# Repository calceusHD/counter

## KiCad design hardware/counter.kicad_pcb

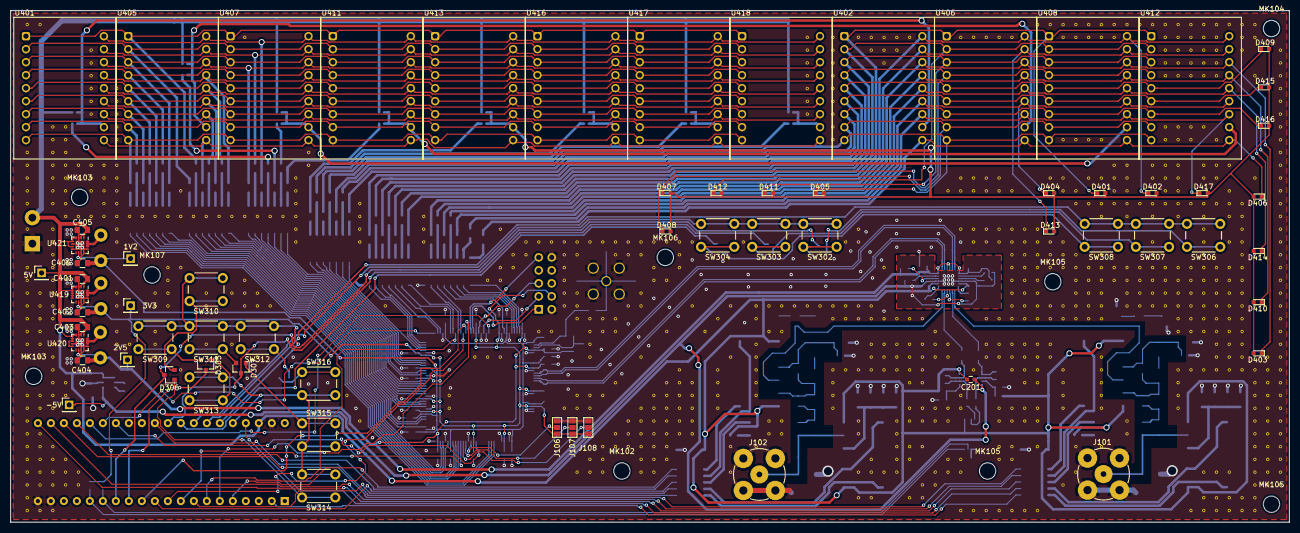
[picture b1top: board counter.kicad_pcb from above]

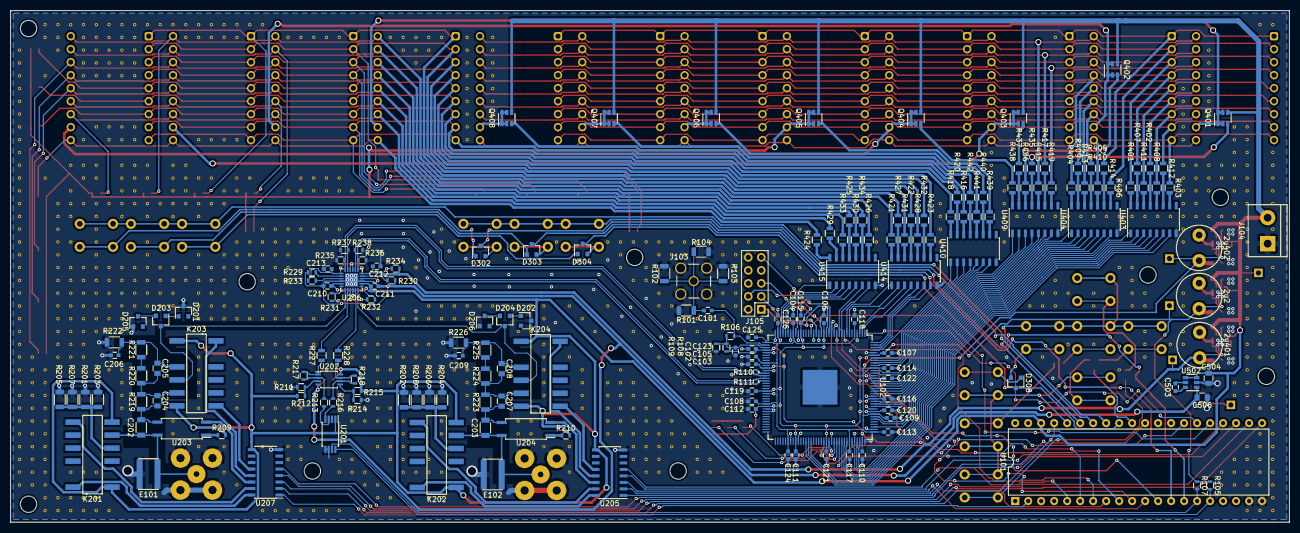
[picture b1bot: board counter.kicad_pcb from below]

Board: 2 copper layers, 250.0 x 100.0 mm, 1050 parts (178 on the bottom side), 249 nets.

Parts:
1V2, 2V5, 3V3, 5V: Test_Point; Pin_Header_Straight_1x01_Pitch2.54mm
2u2, 2u401, 2u402: L_Core_Ferrite; L_Radial_D8.7mm_P5.00mm_Fastron_07HCP
-5V: Test_Point; Pin_Header_Straight_1x01_Pitch2.54mm
C101, C102, C103, C104, C105, C106, C107, C108, C109, C110, C111, C112, C113, C114, C115, C116, C117, C118, C119, C120, C121, C122, C123, C124, C125, C126, C201, C210, C211, C212, C213: 100n; C_0603
C202, C203: 47n 350V; C_1206
C204, C205, C207, C208: 22p; C_0805
C206, C209: 220p; C_0603
C401, C402, C403, C404, C405, C406, C504, C506: 10u 6.3V; C_0805
C503: 1u; C_0603
D201, D202, D205, D206: BZX84C3V6LT1G; D_SOT-23_ANK
D203, D204: BAR64-04; SOT-23
D302, D303, D304, D305, D306, D307, D308: D_x2_ACom_KKA; SOT-23
D401, D402, D403, D404, D405, D406, D407, D408, D409, D410, D411, D412, D413, D414, D415, D416, D417: SML-D12Y1WT86; LED_0603
E101, E102: SPARK_GAP; B88069X4911T902
J101, J102: Conn_Coaxial; BNC-5-1634503-1
J103: Conn_Coaxial; SMA_THT_Jack_Straight
J104: Screw_Terminal_01x02; TerminalBlock_bornier-2_P5.08mm
J105: Conn_02x05_Odd_Even; Pin_Header_Straight_2x05_Pitch2.54mm
J106, J107, J108: GS3
K201, K202, K203, K204: EE2-*TNU; Relay_DPDT_DCLT
MK102, MK103, MK103#2, MK104, MK105, MK105#2, MK105#3, MK106, MK107: Mounting_Hole; MountingHole_3.2mm_M3_ISO7380
Q401, Q402, Q403, Q404, Q405, Q406, Q407, Q408: ZXTP2006E6; SOT-23-6
R101, R102, R103, R104, R201, R202, R203, R204, R205, R206, R207, R208: 200; R_1206
R105, R107, R108, R109: 1k; R_0603
R106: 5k; R_0603
R110, R111: 100; R_0402
R209, R210: 680; R_0603
R211, R214, R217, R218: 20k; R_0603
R212, R213, R215, R216, R229, R230, R233, R234: 10k; R_0603
R219, R223: 510k; R_1206
R220, R224: 390k; R_1206
R221, R222, R225, R226: 50k; R_1206
R227, R228, R435, R436, R437, R438, R439, R440, R441, R442: 150; R_0805
R231, R232: 22k; R_0603
R235, R236, R237, R238: 82; R_0603
R401, R402, R403, R404, R405, R406, R407, R408, R409, R410, R411, R412, R413, R414, R415, R416, R417, R418, R419, R420, R421, R422, R423, R424, R425, R426, R427, R428, R429, R430, R431, R432, R433, R434: 18; R_0805
SW302, SW303, SW304, SW306, SW307, SW308, SW309, SW310, SW311, SW312, SW313, SW314, SW315, SW316: SW_Push; SW_PUSH_6mm
U101: STM32_BLUEPILL; DIP-40_W15.24mm
U102: 10CL006ZE144I8G; EQFP-144_20x20mm_Pitch0.5mm
U201: MCP47FEB02; TSSOP-8_4.4x3mm_Pitch0.65mm
U202: TL972; TSSOP-8_3x3mm_Pitch0.65mm
U203, U204: LH1546; SO-4_7.6x3.6mm_Pitch2.54mm
U205, U207, U403, U404, U409, U410, U414, U415: MC1413; SOIC-16_3.9x9.9mm_Pitch1.27mm
U206: LMH7322; QFN-24-1EP_4x4mm_Pitch0.5mm
U401, U402, U405, U406, U407, U408, U411, U412, U413, U416, U417, U418: 16Segment
U419, U420, U421: SC183C; QFN-16-1EP_3x3mm_Pitch0.5mm
U502: LM2776; SOT-23-6
V2_2, V2_12, V2_13, V2_14, V2_15, V2_16, V2_18, V2_21, V2_22, V2_23, V2_24, V2_25, V2_26, V2_27, V2_28, V2_31, V2_32, V2_33, V2_34, V2_35, V2_36, V2_37, V2_38, V2_39, V2_40, V3_2, V3_23, V3_24, V3_25, V3_26, V3_27, V3_28, V3_31, V3_32, V3_34, V3_35, V3_36, V3_37, V3_38, V3_40, V4_10, V4_11, V4_12, V4_13, V4_14, V4_15, V4_16, V4_18, V4_19, V4_20, V4_21, V4_22, V4_23, V4_24, V4_25, V4_27, V4_28, V4_29, V4_30, V4_31, V4_32, V4_35, V4_36, V4_37, V4_38, V4_40, V5_10, V5_11, V5_12, V5_13, V5_14, V5_15, V5_16, V5_17, V5_30, V5_31, V5_36, V5_37, V5_38, V6_13, V6_14, V6_17, V6_37, V6_38, V7_4, V7_5, V7_6, V7_7, V7_8, V7_9, V7_13, V7_14, V7_15, V7_17, V8_13, V8_14, V8_15, V8_16, V8_17, V9_7, V9_8, V9_9, V9_10, V9_11, V9_13, V9_14, V9_15, V9_16, V9_17, V9_18, V9_19, V9_23, V9_24, V9_26, V9_27, V10_17, V10_27, V11_17, V12_17, V12_23, V12_24, V12_26, V12_27, V12_28, V13_17, V13_21, V13_22, V13_23, V13_24, V14_15, V14_17, V14_21, V14_29, V15_17, V16_17, V16_23, V16_24, V16_27, V17_17, V18_17, V18_23, V18_27, V19_3, V19_17, V19_22, V19_23, V19_24, V20_17, V20_23, V20_24, V20_28, V21_17, V21_24, V22_17, V23_14, V23_15, V23_16, V23_17, V23_18, V23_19, V24_12, V24_13, V27_31, V28_16, V28_17, V28_18, V28_19, V28_33, V30_24, V33_17, V33_18, V33_19, V35_31, V35_32, V37_28, V38_22, V38_28, V39_18, V39_21, V39_22, V39_28, V40_20, V40_21, V41_19, V41_20, V42_19, V42_26, V43_19, V43_26, V44_19, V44_20, V44_21, V44_22, V44_23, V44_24, V44_32, V45_19, V45_20, V45_23, V45_24, V45_25, V45_31, V45_32, V45_37, V46_19, V46_25, V46_26, V46_27, V46_28, V46_31, V46_32, V46_36, V46_37, V47_19, V47_25, V47_26, V47_31, V47_35, V47_36, V47_37, V48_19, V48_20, V48_25, V48_26, V48_30, V48_34, V48_35, V49_19, V49_20, V49_24, V49_33, V49_34, V49_35, V50_19, V50_20, V50_23, V50_24, V50_28, V50_32, V50_33, V50_34, V50_35, V50_36, V50_37, V51_19, V51_21, V51_22, V51_31, V51_32, V51_33, V51_34, V51_35, V51_36, V51_37, V52_19, V52_22, V52_26, V52_30, V52_31, V52_32, V52_33, V52_34, V52_35, V52_36, V53_19, V53_20, V53_21, V53_29, V53_30, V53_31, V53_32, V53_33, V53_34, V54_19, V54_24, V54_30, V54_31, V54_32, V54_33, V54_34, V55_26, V56_25, V56_29, V56_30, V56_31, V56_32, V57_24, V57_28, V57_35, V57_37, V58_19, V59_24, V59_25, V59_27, V59_28, V59_29, V59_30, V59_31, V59_35, V60_24, V60_26, V60_33, V60_34, V61_24, V61_26, V61_33, V61_34, V62_24, V63_3, V63_4, V63_5, V63_6, V63_7, V63_8, V63_9, V63_24, V64_24, V65_3, V65_4, V65_5, V65_6, V65_7, V65_8, V65_9, V65_10, V65_11, V65_24, V65_25, V65_29, V65_30, V65_31, V65_32, V66_19, V66_24, V66_25, V66_29, V67_3, V67_18, V67_19, V67_24, V67_25, V67_29, V67_33, V67_34, V67_37, V67_39, V68_3, V68_4, V68_24, V68_25, V68_27, V68_28, V68_29, V68_36, V68_37, V68_39, V69_3, V69_4, V69_5, V69_21, V69_25, V69_27, V69_28, V69_29, V69_37, V70_3, V70_4, V70_25, V70_27, V70_28, V70_29, V70_33, V70_34, V70_35, V70_36, V70_37, V71_3, V71_25, V71_27, V71_28, V71_29, V71_30, V71_32, V71_33, V71_35, V71_36, V71_39, V72_25, V72_27, V72_28, V72_29, V72_30, V72_32, V72_33, V72_35, V72_38, V72_39, V73_26, V73_27, V73_28, V73_32, V73_33, V73_37, V73_38, V74_15, V74_27, V74_28, V74_32, V74_33, V74_36, V74_37, V74_37#2, V75_3, V75_14, V75_15, V75_18, V75_31, V75_32, V75_36, V75_40, V76_3, V76_14, V76_15, V76_18, V76_19, V76_29, V76_40, V77_3, V77_14, V77_15, V77_18, V77_19, V77_25, V77_27, V77_28, V77_40, V78_3, V78_14, V78_15, V78_18, V78_19, V78_25, V78_27, V78_28, V78_32, V78_33, V78_35, V78_36, V78_40, V79_3, V79_15, V79_18, V79_19, V79_20, V79_21, V79_22, V79_23, V79_24, V79_25, V79_27, V79_28, V79_29, V79_32, V79_33, V79_35, V79_36, V79_40, V80_18, V80_19, V80_20, V80_21, V80_22, V80_23, V80_24, V80_25, V80_27, V80_28, V80_29, V80_30, V80_32, V80_33, V80_40, V81_2, V81_18, V81_19, V81_20, V81_21, V81_22, V81_23, V81_24, V81_25, V81_27, V81_28, V81_29, V81_30, V81_32, V81_33, V81_35, V81_40, V82_2, V82_14, V82_19, V82_20, V82_21, V82_24, V82_25, V82_27, V82_28, V83_2, V83_3, V83_11, V83_14, V83_15, V83_19, V83_20, V83_21, V83_24, V83_25, V83_29, V83_30, V83_31, V83_32, V83_38, V84_2, V84_3, V84_11, V84_15, V84_16, V84_20, V84_21, V84_22, V84_23, V84_24, V84_25, V84_35, V84_37, V85_2, V85_3, V85_11, V85_14, V85_16, V85_21, V85_22, V85_23, V85_24, V85_25, V86_2, V86_3, V86_11, V86_14, V86_16, V86_17, V86_20, V86_21, V86_22, V86_23, V86_24, V86_25, V86_28, V86_29, V86_30, V86_31, V86_32, V86_35, V87_2, V87_3, V87_13, V87_14, V87_15, V87_16, V87_21, V87_22, V88_2, V88_13, V88_14, V88_15, V88_16, V88_17, V88_21, V88_22, V88_23, V88_24, V88_33, V88_34, V89_2, V89_16, V89_21, V89_22, V89_23, V89_24, V90_2, V90_13, V90_14, V90_16, V90_17, V90_19, V90_20, V90_21, V90_22, V90_23, V90_24, V91_2, V91_3, V91_4, V91_5, V91_6, V91_10, V91_11, V91_13, V91_14, V91_15, V91_16, V91_21, V91_22, V91_23, V91_24, V92_2, V92_3, V92_4, V92_5, V92_6, V92_10, V92_11, V92_13, V92_14, V92_15, V92_16, V92_17, V92_21, V92_22, V92_23, V92_24, V92_25, V92_26, V92_29, V92_30, V92_31, V92_32, V93_2, V93_3, V93_4, V93_5, V93_6, V93_10, V93_11, V93_16, V93_21, V93_22, V93_23, V93_24, V93_25, V93_26, V93_29, V93_40, V94_2, V94_3, V94_4, V94_5, V94_6, V94_10, V94_13, V94_14, V94_16, V94_17, V94_18, V94_19, V94_20, V94_21, V94_22, V94_23, V94_24, V94_25, V94_26, V94_29, V94_37, V94_39, V94_40, V95_2, V95_3, V95_4, V95_5, V95_6, V95_11, V95_13, V95_14, V95_16, V95_21, V95_22, V95_23, V95_24, V95_25, V95_26, V95_27, V95_28, V95_29, V95_37, V95_39, V95_40, V96_2, V96_13, V96_15, V96_16, V96_17, V96_19, V96_21, V96_22, V96_23, V96_24, V96_25, V96_26, V96_27, V96_28, V96_29, V96_37, V96_39, V96_40, V97_2, V97_3, V97_4, V97_16, V97_17, V97_18, V97_19, V97_20, V97_21, V97_22, V97_23, V97_24, V97_25, V97_26, V97_27, V97_28, V97_29, V97_39, V97_40, V98_2, V98_3, V98_6, V98_14, V98_29, V98_30, V98_31, V98_32, V98_33, V98_34, V98_35, V98_36, V98_37, V98_38, V98_39, V98_40, V99_28, V99_29, V99_30, V99_31, V99_32, V99_33, V99_34, V99_35, V99_36, V99_37, V99_38, V100_4, V100_5, V100_6, V100_7, V100_8, V100_9, V100_10, V100_11, V100_12, V100_13, V100_14, V100_15, V100_16, V100_17, V100_18, V100_19, V100_20, V100_21, V100_22, V100_23, V100_24, V100_25, V100_26, V100_27, V100_28, V100_29, V100_30, V100_31, V100_32, V100_33, V100_34, V100_35, V100_36, V100_37, V100_38: AUTO_VIA; VIA_MATRIX

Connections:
+1V2: 1V2.1, 2u402.2, C103.1, C104.2, C108.1, C109.2, C113.1, C114.2, C117.1, C118.2, C124.2, C125.2, C406.2, U102.5, U102.29, U102.37, U102.45, U102.61, U102.78, U102.102, U102.109, U102.116, U102.134, U421.10
+2V5: 2V5.1, 2u401.2, C105.2, C110.2, C123.2, C126.2, C212.2, C213.2, C404.2, R108.1, R233.2, R234.2, U102.35, U102.40, U102.47, U102.107, U206.1, U206.18, U206.21, U206.22, U420.10
+3V3: 2u2.2, 3V3.1, C106.2, C107.2, C111.2, C112.2, C115.2, C116.2, C119.2, C120.2, C121.2, C122.2, C402.2, J105.4, J106.3, J107.3, J108.3, R105.1, R107.1, U102.17, U102.26, U102.56, U102.62, U102.81, U102.93, U102.117, U102.122, U102.130, U102.139, U419.10
+5V: 5V.1, C201.2, C210.1, C211.1, C401.2, C403.2, C405.2, C504.1, J104.2, K201.1, K201.6, K202.1, K202.6, K203.1, K203.6, K204.1, K204.6, Q401.4, Q402.4, Q403.4, Q404.4, Q405.4, Q406.4, Q407.4, Q408.4, R209.2, R210.2, R212.2, R215.2, U101.38, U201.1, U202.8, U205.9, U206.5, U206.14, U207.9, U419.1, U419.2, U419.4, U419.5, U419.6, U419.7, U419.8, U420.1, U420.2, U420.4, U420.5, U420.6, U420.8, U421.1, U421.2, U421.4, U421.5, U421.7, U502.3, U502.4
-5V: -5V.1, C201.1, C210.2, C211.2, C506.2, R229.2, R230.2, U202.4, U206.4, U206.15, U206.25, U502.1
/50Ohm_OFF_1: U101.37, U207.2
/50Ohm_OFF_2: U101.8, U205.2
/50Ohm_ON_1: U101.2, U207.1
/50Ohm_ON_2: U101.30, U205.1
/A0: U102.126, U409.4
/A1: U102.127, U409.3
/A2: U102.128, U409.2
/A3: U102.129, U409.1
/A4: U102.132, U410.7
/A5: U102.133, U410.6
/A6: U102.135, U410.5
/A7: U102.136, U410.4
/AC_1: U101.21, U207.3
/AC_2: U101.11, U205.3
/AFE/50Ohm_OFF_1_int: K201.7, U207.15
/AFE/50Ohm_OFF_2_int: K202.7, U205.15
/AFE/50Ohm_ON_1_int: K201.12, U207.16
/AFE/50Ohm_ON_2_int: K202.12, U205.16
/AFE/AC_1_int: U203.2, U207.14
/AFE/AC_2_int: U204.2, U205.14
/AFE/CH1_IN: C202.2, E101.1, J101.1, K201.5, U203.4
/AFE/CH2_IN: C203.2, E102.1, J102.1, K202.5, U204.4
/AFE/DIV10_OFF_1_int: K203.7, U207.12
/AFE/DIV10_OFF_2_int: K204.7, U205.12
/AFE/DIV10_ON_1_int: K203.12, U207.13
/AFE/DIV10_ON_2_int: K204.12, U205.13
/AFE/VOFF2: R228.1, U206.11
/AFE/VOFF_1: R227.1, U206.8
/C0: SW302.2, SW303.2, SW304.2, U101.33
/C0_1: U102.106, U404.6
/C0_2: U102.7, U414.2
/C1: SW306.2, SW307.2, SW308.2, U101.34
/C1_1: U102.125, U409.5
/C1_2: U102.8, U414.1
/C2: SW309.2, SW310.2, SW311.2, SW312.2, U101.35
/C2_1: U102.121, U409.7
/C2_2: U102.11, U415.6
/C3: SW313.2, SW314.2, SW315.2, SW316.2, U101.36
/C3_1: U102.115, U404.3
/C3_2: U102.32, U415.3
/C4_1: U102.85, U403.7
/C4_2: U102.137, U410.3
/C5_1: U102.111, U404.5
/C5_2: U102.34, U415.1
/C6_1: U102.86, U403.6
/C6_2: U102.138, U410.2
/C7_1: U102.101, U403.2
/C7_2: U102.144, U414.5
/C8_1: U102.100, U403.3
/C8_2: U102.143, U414.6
/C9_1: U102.120, U404.1
/C9_2: U102.28, U415.5
/C10_1: U102.103, U403.1
/C10_2: U102.2, U414.4
/C11_1: U102.105, U404.7
/C11_2: U102.3, U414.3
/C12_1: U102.124, U409.6
/C12_2: U102.10, U415.7
/C13_1: U102.119, U404.2
/C13_2: U102.31, U415.4
/C14_1: U102.99, U403.4
/C14_2: U102.142, U414.7
/C15_1: U102.87, U403.5
/C15_2: U102.141, U410.1
/C16_1: U102.114, U404.4
/C16_2: U102.33, U415.2
/CH1+: R110.2, R237.2, U102.50, U206.23
/CH1-: R110.1, R235.2, U102.49, U206.24
/CH2+: R111.2, R238.2, U102.51, U206.20
/CH2-: R111.1, R236.2, U102.52, U206.19
/CLKIN_n: C102.2, R106.2, R108.2, R109.1, U102.39
/CLKIN_p: C101.1, R106.1, U102.38
/CONF_DONE: U101.27, U102.92
/DATA0: U101.12, U102.13
/DCLK: U101.10, U102.12
/DIV10_OFF_1: U101.23, U207.5
/DIV10_OFF_2: U101.5, U205.5
/DIV10_ON_1: U101.22, U207.4
/DIV10_ON_2: U101.24, U205.4
/INIT_DONE: U101.9, U102.98
/INTCLK: U101.25, U102.22
/LED_array/A0: Q401.1, Q401.2, Q401.5, Q401.6, U401.11, U402.11
/LED_array/A1: Q402.1, Q402.2, Q402.5, Q402.6, U405.11, U406.11
/LED_array/A1_1: R414.1, U401.1, U405.1, U407.1, U411.1, U413.1, U416.1, U417.1, U418.1
/LED_array/A1_2: D401.1, R427.1, U402.1, U406.1, U408.1, U412.1
/LED_array/A2: Q403.1, Q403.2, Q403.5, Q403.6, U407.11, U408.11
/LED_array/A2_1: R415.1, U401.18, U405.18, U407.18, U411.18, U413.18, U416.18, U417.18, U418.18
/LED_array/A2_2: D402.1, R421.1, U402.18, U406.18, U408.18, U412.18
/LED_array/A3: Q404.1, Q404.2, Q404.5, Q404.6, U411.11, U412.11
/LED_array/A4: D401.2, D402.2, D403.2, D404.2, D405.2, D406.2, D407.2, D408.2, D409.2, D410.2, D411.2, D412.2, D413.2, D414.2, D415.2, D416.2, D417.2, Q405.1, Q405.2, Q405.5, Q405.6, U413.11
/LED_array/A5: Q406.1, Q406.2, Q406.5, Q406.6, U416.11
/LED_array/A6: Q407.1, Q407.2, Q407.5, Q407.6, U417.11
/LED_array/A7: Q408.1, Q408.2, Q408.5, Q408.6, U418.11
/LED_array/B_1: R419.1, U401.16, U405.16, U407.16, U411.16, U413.16, U416.16, U417.16, U418.16
/LED_array/B_2: D403.1, R434.1, U402.16, U406.16, U408.16, U412.16
/LED_array/C_1: R413.1, U401.13, U405.13, U407.13, U411.13, U413.13, U416.13, U417.13, U418.13
/LED_array/C_2: D404.1, R433.1, U402.13, U406.13, U408.13, U412.13
/LED_array/D1_1: R403.1, U401.9, U405.9, U407.9, U411.9, U413.9, U416.9, U417.9, U418.9
/LED_array/D1_2: D405.1, R416.1, U402.9, U406.9, U408.9, U412.9
/LED_array/D2_1: R410.1, U401.10, U405.10, U407.10, U411.10, U413.10, U416.10, U417.10, U418.10
/LED_array/D2_2: D406.1, R424.1, U402.10, U406.10, U408.10, U412.10
/LED_array/DP_1: R405.1, U401.12, U405.12, U407.12, U411.12, U413.12, U416.12, U417.12, U418.12
/LED_array/DP_2: D417.1, R429.1, U402.12, U406.12, U408.12, U412.12
/LED_array/DR0: R435.2, U409.13
/LED_array/DR1: R436.2, U409.14
/LED_array/DR2: R437.2, U409.15
/LED_array/DR3: R438.2, U409.16
/LED_array/DR4: R439.2, U410.10
/LED_array/DR5: R440.2, U410.11
/LED_array/DR6: R441.2, U410.12
/LED_array/DR7: R442.2, U410.13
/LED_array/E_1: R412.1, U401.8, U405.8, U407.8, U411.8, U413.8, U416.8, U417.8, U418.8
/LED_array/E_2: D407.1, R420.1, U402.8, U406.8, U408.8, U412.8
/LED_array/F_1: R407.1, U401.4, U405.4, U407.4, U411.4, U413.4, U416.4, U417.4, U418.4
/LED_array/F_2: D408.1, R428.1, U402.4, U406.4, U408.4, U412.4
/LED_array/G1_1: R411.1, U401.5, U405.5, U407.5, U411.5, U413.5, U416.5, U417.5, U418.5
/LED_array/G1_2: D409.1, R432.1, U402.5, U406.5, U408.5, U412.5
/LED_array/G2_1: R404.1, U401.15, U405.15, U407.15, U411.15, U413.15, U416.15, U417.15, U418.15
/LED_array/G2_2: D410.1, R430.1, U402.15, U406.15, U408.15, U412.15
/LED_array/H_1: R401.1, U401.3, U405.3, U407.3, U411.3, U413.3, U416.3, U417.3, U418.3
/LED_array/H_2: D411.1, R422.1, U402.3, U406.3, U408.3, U412.3
/LED_array/J_1: R406.1, U401.2, U405.2, U407.2, U411.2, U413.2, U416.2, U417.2, U418.2
/LED_array/J_2: D412.1, R431.1, U402.2, U406.2, U408.2, U412.2
/LED_array/K_1: R417.1, U401.17, U405.17, U407.17, U411.17, U413.17, U416.17, U417.17, U418.17
/LED_array/K_2: D413.1, R426.1, U402.17, U406.17, U408.17, U412.17
/LED_array/L_1: R409.1, U401.14, U405.14, U407.14, U411.14, U413.14, U416.14, U417.14, U418.14
/LED_array/L_2: D414.1, R425.1, U402.14, U406.14, U408.14, U412.14
/LED_array/M_1: R402.1, U401.6, U405.6, U407.6, U411.6, U413.6, U416.6, U417.6, U418.6
/LED_array/M_2: D415.1, R423.1, U402.6, U406.6, U408.6, U412.6
/LED_array/N_1: R408.1, U401.7, U405.7, U407.7, U411.7, U413.7, U416.7, U417.7, U418.7
/LED_array/N_2: D416.1, R418.1, U402.7, U406.7, U408.7, U412.7
/MSEL0: J106.2, U102.94
/MSEL1: J107.2, U102.96
/MSEL2: J108.2, U102.97
/R0: D305.3, U101.13
/R1: D302.3, D306.3, U101.14
/R2: D303.3, D307.3, U101.31
/R3: D304.3, D308.3, U101.32
/SCL: R107.2, U101.15, U201.7
/SDA: R105.2, U101.16, U201.8
/TCK: J105.1, U102.16
/TDI: J105.9, U102.15
/TDO: J105.3, U102.20
/TMS: J105.5, U102.18
/TXD: U101.26, U102.1
/~CONFIG: U101.6, U102.14
/~STATUS: U101.7, U102.9
GND: C102.1, C103.2, C104.1, C105.1, C106.1, C107.1, C108.2, C109.1, C110.1, C111.1, C112.1, C113.2, C114.1, C115.1, C116.1, C117.2, C118.1, C119.1, C120.1, C121.1, C122.1, C123.1, C124.1, C125.1, C126.1, C206.1, C209.1, C212.1, C213.1, C401.1, C402.1, C403.1, C404.1, C405.1, C406.1, C504.2, C506.1, D201.1, D202.1, D205.2, D206.2, E101.2, E102.2, J101.2, J102.2, J103.2, J104.1, J105.2, J105.10, J106.1, J107.1, J108.1, R101.2, R102.2, R103.2, R104.2, R109.2, R201.2, R202.2, R203.2, R204.2, R205.2, R206.2, R207.2, R208.2, R211.2, R214.2, R222.2, R226.2, R235.1, R236.1, R237.1, R238.1, U101.19, U101.20, U101.39, U102.4, U102.19, U102.21, U102.27, U102.30, U102.36, U102.41, U102.48, U102.57, U102.63, U102.64, U102.79, U102.82, U102.95, U102.104, U102.108, U102.110, U102.118, U102.123, U102.131, U102.140, U102.145, U201.5, U201.6, U205.8, U207.8, U403.8, U404.8, U409.8, U410.8, U414.8, U415.8, U419.3, U419.11, U419.12, U419.13, U419.17, U420.3, U420.7, U420.11, U420.12, U420.13, U420.17, U421.3, U421.6, U421.8, U421.11, U421.12, U421.13, U421.17, U502.2, V2_2.1, V2_12.1, V2_13.1, V2_14.1, V2_15.1, V2_16.1, V2_18.1, V2_21.1, V2_22.1, V2_23.1, V2_24.1, V2_25.1, V2_26.1, V2_27.1, V2_28.1, V2_31.1, V2_32.1, V2_33.1, V2_34.1, V2_35.1, V2_36.1, V2_37.1, V2_38.1, V2_39.1, V2_40.1, V3_2.1, V3_23.1, V3_24.1, V3_25.1, V3_26.1, V3_27.1, V3_28.1, V3_31.1, V3_32.1, V3_34.1, V3_35.1, V3_36.1, V3_37.1, V3_38.1, V3_40.1, V4_10.1, V4_11.1, V4_12.1, V4_13.1, V4_14.1, V4_15.1, V4_16.1, V4_18.1, V4_19.1, V4_20.1, V4_21.1, V4_22.1, V4_23.1, V4_24.1, V4_25.1, V4_27.1, V4_28.1, V4_29.1, V4_30.1, V4_31.1, V4_32.1, V4_35.1, V4_36.1, V4_37.1, V4_38.1, V4_40.1, V5_10.1, V5_11.1, V5_12.1, V5_13.1, V5_14.1, V5_15.1, V5_16.1, V5_17.1, V5_30.1, V5_31.1, V5_36.1, V5_37.1, V5_38.1, V6_13.1, V6_14.1, V6_17.1, V6_37.1, V6_38.1, V7_4.1, V7_5.1, V7_6.1, V7_7.1, V7_8.1, V7_9.1, V7_13.1, V7_14.1, V7_15.1, V7_17.1, V8_13.1, V8_14.1, V8_15.1, V8_16.1, V8_17.1, V9_7.1, V9_8.1, V9_9.1, V9_10.1, V9_11.1, V9_13.1, V9_14.1, V9_15.1, V9_16.1, V9_17.1, V9_18.1, V9_19.1, V9_23.1, V9_24.1, V9_26.1, V9_27.1, V10_17.1, V10_27.1, V11_17.1, V12_17.1, V12_23.1, V12_24.1, V12_26.1, V12_27.1, V12_28.1, V13_17.1, V13_21.1, V13_22.1, V13_23.1, V13_24.1, V14_15.1, V14_17.1, V14_21.1, V14_29.1, V15_17.1, V16_17.1, V16_23.1, V16_24.1, V16_27.1, V17_17.1, V18_17.1, V18_23.1, V18_27.1, V19_3.1, V19_17.1, V19_22.1, V19_23.1, V19_24.1, V20_17.1, V20_23.1, V20_24.1, V20_28.1, V21_17.1, V21_24.1, V22_17.1, V23_14.1, V23_15.1, V23_16.1, V23_17.1, V23_18.1, V23_19.1, V24_12.1, V24_13.1, V27_31.1, V28_16.1, V28_17.1, V28_18.1, V28_19.1, V28_33.1, V30_24.1, V33_17.1, V33_18.1, V33_19.1, V35_31.1, V35_32.1, V37_28.1, V38_22.1, V38_28.1, V39_18.1, V39_21.1, V39_22.1, V39_28.1, V40_20.1, V40_21.1, V41_19.1, V41_20.1, V42_19.1, V42_26.1, V43_19.1, V43_26.1, V44_19.1, V44_20.1, V44_21.1, V44_22.1, V44_23.1, V44_24.1, V44_32.1, V45_19.1, V45_20.1, V45_23.1, V45_24.1, V45_25.1, V45_31.1, V45_32.1, V45_37.1, V46_19.1, V46_25.1, V46_26.1, V46_27.1, V46_28.1, V46_31.1, V46_32.1, V46_36.1, V46_37.1, V47_19.1, V47_25.1, V47_26.1, V47_31.1, V47_35.1, V47_36.1, V47_37.1, V48_19.1, V48_20.1, V48_25.1, V48_26.1, V48_30.1, V48_34.1, V48_35.1, V49_19.1, V49_20.1, V49_24.1, V49_33.1, V49_34.1, V49_35.1, V50_19.1, V50_20.1, V50_23.1, V50_24.1, V50_28.1, V50_32.1, V50_33.1, V50_34.1, V50_35.1, V50_36.1, V50_37.1, V51_19.1, V51_21.1, V51_22.1, V51_31.1, V51_32.1, V51_33.1, V51_34.1, V51_35.1, V51_36.1, V51_37.1, V52_19.1, V52_22.1, V52_26.1, V52_30.1, V52_31.1, V52_32.1, V52_33.1, V52_34.1, V52_35.1, V52_36.1, V53_19.1, V53_20.1, V53_21.1, V53_29.1, V53_30.1, V53_31.1, V53_32.1, V53_33.1, V53_34.1, V54_19.1, V54_24.1, V54_30.1, V54_31.1, V54_32.1, V54_33.1, V54_34.1, V55_26.1, V56_25.1, V56_29.1, V56_30.1, V56_31.1, V56_32.1, V57_24.1, V57_28.1, V57_35.1, V57_37.1, V58_19.1, V59_24.1, V59_25.1, V59_27.1, V59_28.1, V59_29.1, V59_30.1, V59_31.1, V59_35.1, V60_24.1, V60_26.1, V60_33.1, V60_34.1, V61_24.1, V61_26.1, V61_33.1, V61_34.1, V62_24.1, V63_3.1, V63_4.1, V63_5.1, V63_6.1, V63_7.1, V63_8.1, V63_9.1, V63_24.1, V64_24.1, V65_3.1, V65_4.1, V65_5.1, V65_6.1, V65_7.1, V65_8.1, V65_9.1, V65_10.1, V65_11.1, V65_24.1, V65_25.1, V65_29.1, V65_30.1, V65_31.1, V65_32.1, V66_19.1, V66_24.1, V66_25.1, V66_29.1, V67_3.1, V67_18.1, V67_19.1, V67_24.1, V67_25.1, V67_29.1, V67_33.1, V67_34.1, V67_37.1, V67_39.1, V68_3.1, V68_4.1, V68_24.1, V68_25.1, V68_27.1, V68_28.1, V68_29.1, V68_36.1, V68_37.1, V68_39.1, V69_3.1, V69_4.1, V69_5.1, V69_21.1, V69_25.1, V69_27.1, V69_28.1, V69_29.1, V69_37.1, V70_3.1, V70_4.1, V70_25.1, V70_27.1, V70_28.1, V70_29.1, V70_33.1, V70_34.1, V70_35.1, V70_36.1, V70_37.1, V71_3.1, V71_25.1, V71_27.1, V71_28.1, V71_29.1, V71_30.1, V71_32.1, V71_33.1, V71_35.1, V71_36.1, V71_39.1, V72_25.1, V72_27.1, V72_28.1, V72_29.1, V72_30.1, V72_32.1, V72_33.1, V72_35.1, V72_38.1, V72_39.1, V73_26.1, V73_27.1, V73_28.1, V73_32.1, V73_33.1, V73_37.1, V73_38.1, V74_15.1, V74_27.1, V74_28.1, V74_32.1, V74_33.1, V74_36.1, V74_37.1, V74_37#2.1, V75_3.1, V75_14.1, V75_15.1, V75_18.1, V75_31.1, V75_32.1, V75_36.1, V75_40.1, V76_3.1, V76_14.1, V76_15.1, V76_18.1, V76_19.1, V76_29.1, V76_40.1, V77_3.1, V77_14.1, V77_15.1, V77_18.1, V77_19.1, V77_25.1, V77_27.1, V77_28.1, V77_40.1, V78_3.1, V78_14.1, V78_15.1, V78_18.1, V78_19.1, V78_25.1, V78_27.1, V78_28.1, V78_32.1, V78_33.1, V78_35.1, V78_36.1, V78_40.1, V79_3.1, V79_15.1, V79_18.1, V79_19.1, V79_20.1, V79_21.1, V79_22.1, V79_23.1, V79_24.1, V79_25.1, V79_27.1, V79_28.1, V79_29.1, V79_32.1, V79_33.1, V79_35.1, V79_36.1, V79_40.1, V80_18.1, V80_19.1, V80_20.1, V80_21.1, V80_22.1, V80_23.1, V80_24.1, V80_25.1, V80_27.1, V80_28.1, V80_29.1, V80_30.1, V80_32.1, V80_33.1, V80_40.1, V81_2.1, V81_18.1, V81_19.1, V81_20.1, V81_21.1, V81_22.1, V81_23.1, V81_24.1, V81_25.1, V81_27.1, V81_28.1, V81_29.1, V81_30.1, V81_32.1, V81_33.1, V81_35.1, V81_40.1, V82_2.1, V82_14.1, V82_19.1, V82_20.1, V82_21.1, V82_24.1, V82_25.1, V82_27.1, V82_28.1, V83_2.1, V83_3.1, V83_11.1, V83_14.1, V83_15.1, V83_19.1, V83_20.1, V83_21.1, V83_24.1, V83_25.1, V83_29.1, V83_30.1, V83_31.1, V83_32.1, V83_38.1, V84_2.1, V84_3.1, V84_11.1, V84_15.1, V84_16.1, V84_20.1, V84_21.1, V84_22.1, V84_23.1, V84_24.1, V84_25.1, V84_35.1, V84_37.1, V85_2.1, V85_3.1, V85_11.1, V85_14.1, V85_16.1, V85_21.1, V85_22.1, V85_23.1, V85_24.1, V85_25.1, V86_2.1, V86_3.1, V86_11.1, V86_14.1, V86_16.1, V86_17.1, V86_20.1, V86_21.1, V86_22.1, V86_23.1, V86_24.1, V86_25.1, V86_28.1, V86_29.1, V86_30.1, V86_31.1, V86_32.1, V86_35.1, V87_2.1, V87_3.1, V87_13.1, V87_14.1, V87_15.1, V87_16.1, V87_21.1, V87_22.1, V88_2.1, V88_13.1, V88_14.1, V88_15.1, V88_16.1, V88_17.1, V88_21.1, V88_22.1, V88_23.1, V88_24.1, V88_33.1, V88_34.1, V89_2.1, V89_16.1, V89_21.1, V89_22.1, V89_23.1, V89_24.1, V90_2.1, V90_13.1, V90_14.1, V90_16.1, V90_17.1, V90_19.1, V90_20.1, V90_21.1, V90_22.1, V90_23.1, V90_24.1, V91_2.1, V91_3.1, V91_4.1, V91_5.1, V91_6.1, V91_10.1, V91_11.1, V91_13.1, V91_14.1, V91_15.1, V91_16.1, V91_21.1, V91_22.1, V91_23.1, V91_24.1, V92_2.1, V92_3.1, V92_4.1, V92_5.1, V92_6.1, V92_10.1, V92_11.1, V92_13.1, V92_14.1, V92_15.1, V92_16.1, V92_17.1, V92_21.1, V92_22.1, V92_23.1, V92_24.1, V92_25.1, V92_26.1, V92_29.1, V92_30.1, V92_31.1, V92_32.1, V93_2.1, V93_3.1, V93_4.1, V93_5.1, V93_6.1, V93_10.1, V93_11.1, V93_16.1, V93_21.1, V93_22.1, V93_23.1, V93_24.1, V93_25.1, V93_26.1, V93_29.1, V93_40.1, V94_2.1, V94_3.1, V94_4.1, V94_5.1, V94_6.1, V94_10.1, V94_13.1, V94_14.1, V94_16.1, V94_17.1, V94_18.1, V94_19.1, V94_20.1, V94_21.1, V94_22.1, V94_23.1, V94_24.1, V94_25.1, V94_26.1, V94_29.1, V94_37.1, V94_39.1, V94_40.1, V95_2.1, V95_3.1, V95_4.1, V95_5.1, V95_6.1, V95_11.1, V95_13.1, V95_14.1, V95_16.1, V95_21.1, V95_22.1, V95_23.1, V95_24.1, V95_25.1, V95_26.1, V95_27.1, V95_28.1, V95_29.1, V95_37.1, V95_39.1, V95_40.1, V96_2.1, V96_13.1, V96_15.1, V96_16.1, V96_17.1, V96_19.1, V96_21.1, V96_22.1, V96_23.1, V96_24.1, V96_25.1, V96_26.1, V96_27.1, V96_28.1, V96_29.1, V96_37.1, V96_39.1, V96_40.1, V97_2.1, V97_3.1, V97_4.1, V97_16.1, V97_17.1, V97_18.1, V97_19.1, V97_20.1, V97_21.1, V97_22.1, V97_23.1, V97_24.1, V97_25.1, V97_26.1, V97_27.1, V97_28.1, V97_29.1, V97_39.1, V97_40.1, V98_2.1, V98_3.1, V98_6.1, V98_14.1, V98_29.1, V98_30.1, V98_31.1, V98_32.1, V98_33.1, V98_34.1, V98_35.1, V98_36.1, V98_37.1, V98_38.1, V98_39.1, V98_40.1, V99_28.1, V99_29.1, V99_30.1, V99_31.1, V99_32.1, V99_33.1, V99_34.1, V99_35.1, V99_36.1, V99_37.1, V99_38.1, V100_4.1, V100_5.1, V100_6.1, V100_7.1, V100_8.1, V100_9.1, V100_10.1, V100_11.1, V100_12.1, V100_13.1, V100_14.1, V100_15.1, V100_16.1, V100_17.1, V100_18.1, V100_19.1, V100_20.1, V100_21.1, V100_22.1, V100_23.1, V100_24.1, V100_25.1, V100_26.1, V100_27.1, V100_28.1, V100_29.1, V100_30.1, V100_31.1, V100_32.1, V100_33.1, V100_34.1, V100_35.1, V100_36.1, V100_37.1, V100_38.1
unnamed: 2u2.1, U419.14, U419.15, U419.16
unnamed: 2u401.1, U420.14, U420.15, U420.16
unnamed: 2u402.1, U421.14, U421.15, U421.16
unnamed: C101.2, J103.1, R101.1, R102.1, R103.1, R104.1
unnamed: C202.1, C204.2, R219.1, U203.3
unnamed: C203.1, C207.2, R223.1, U204.3
unnamed: C204.1, C205.2, K203.5, R219.2, R220.1
unnamed: C205.1, C206.2, K203.3, R221.2, R222.1
unnamed: C207.1, C208.2, K204.5, R223.2, R224.1
unnamed: C208.1, C209.2, K204.3, R225.2, R226.1
unnamed: C503.1, U502.5
unnamed: C503.2, U502.6
unnamed: D201.2, D203.1
unnamed: D202.2, D204.1
unnamed: D203.2, D205.1
unnamed: D203.3, K203.4, U206.7
unnamed: D204.2, D206.1
unnamed: D204.3, K204.4, U206.12
unnamed: D302.1, SW306.1
unnamed: D302.2, SW302.1
unnamed: D303.1, SW307.1
unnamed: D303.2, SW303.1
unnamed: D304.1, SW308.1
unnamed: D304.2, SW304.1
unnamed: D305.1, SW313.1
unnamed: D305.2, SW309.1
unnamed: D306.1, SW314.1
unnamed: D306.2, SW310.1
unnamed: D307.1, SW315.1
unnamed: D307.2, SW311.1
unnamed: D308.1, SW316.1
unnamed: D308.2, SW312.1
unnamed: K201.4, R201.1, R203.1, R205.1, R207.1
unnamed: K202.4, R202.1, R204.1, R206.1, R208.1
unnamed: Q401.3, R435.1
unnamed: Q402.3, R436.1
unnamed: Q403.3, R437.1
unnamed: Q404.3, R438.1
unnamed: Q405.3, R439.1
unnamed: Q406.3, R440.1
unnamed: Q407.3, R441.1
unnamed: Q408.3, R442.1
unnamed: R209.1, U203.1
unnamed: R210.1, U204.1
unnamed: R211.1, R212.1, U202.3
unnamed: R213.1, R217.1, U202.2
unnamed: R213.2, U201.3
unnamed: R214.1, R215.1, U202.5
unnamed: R216.1, R218.1, U202.6
unnamed: R216.2, U201.4
unnamed: R217.2, R227.2, U202.1
unnamed: R218.2, R228.2, U202.7
unnamed: R220.2, R221.1
unnamed: R224.2, R225.1
unnamed: R229.1, U206.2
unnamed: R230.1, U206.17
unnamed: R231.1, U206.6
unnamed: R231.2, U206.9
unnamed: R232.1, U206.13
unnamed: R232.2, U206.10
unnamed: R233.1, U206.3
unnamed: R234.1, U206.16
unnamed: R401.2, U403.16
unnamed: R402.2, U403.13
unnamed: R403.2, U403.10
unnamed: R404.2, U404.16
unnamed: R405.2, U404.13
unnamed: R406.2, U404.10
unnamed: R407.2, U403.15
unnamed: R408.2, U403.12
unnamed: R409.2, U404.15
unnamed: R410.2, U404.12
unnamed: R411.2, U403.14
unnamed: R412.2, U403.11
unnamed: R413.2, U404.14
unnamed: R414.2, U404.11
unnamed: R415.2, U409.12
unnamed: R416.2, U410.14
unnamed: R417.2, U409.11
unnamed: R418.2, U410.16
unnamed: R419.2, U409.10
unnamed: R420.2, U410.15
unnamed: R421.2, U414.16
unnamed: R422.2, U414.13
unnamed: R423.2, U414.10
unnamed: R424.2, U415.16
unnamed: R425.2, U415.13
unnamed: R426.2, U415.10
unnamed: R427.2, U414.15
unnamed: R428.2, U414.12
unnamed: R429.2, U415.15
unnamed: R430.2, U415.12
unnamed: R431.2, U414.14
unnamed: R432.2, U414.11
unnamed: R433.2, U415.14
unnamed: R434.2, U415.11

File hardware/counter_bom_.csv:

Component,Description,Part,References,Value,Footprint,Quantity Per PCB,Datasheet
1,Inductor with Ferrite Core,L_Core_Ferrite,2u2 2u401 2u402,L_Core_Ferrite,L_Radial_D8.7mm_P5.00mm_Fastron_07HCP,3,
2,Unpolarized capacitor,C,C101 C102 C103 C104 C105 C106 C107 C108 C109 C110 C111 C112 C113 C114 C115 C116 C117 C118 C119 C120 C121 C122 C123 C124 C125 C126 C201 C210 C211 C212 C213,100n,C_0603,31,
3,Unpolarized capacitor,C,C401 C402 C403 C404 C405 C406 C504 C506,10u 6.3V,C_0805,8,
4,Unpolarized capacitor,C,C503,1u,C_0603,1,
5,Unpolarized capacitor,C,C206 C209,220p,C_0603,2,
6,Unpolarized capacitor,C,C204 C205 C207 C208,22p,C_0805,4,
7,Unpolarized capacitor,C,C202 C203,47n 350V,C_1206,2,
8,Dual diode,D_x2_Serial_AKC,D203 D204,BAR64-04,SOT-23,2,
9,Zener Diode,D_Zener,D201 D202 D205 D206,BZX84C3V6LT1G,D_SOT-23_ANK,4,https://en.wikipedia.org/wiki/Zener_diode
10,"Dual diode, common anode",D_x2_ACom_KKA,D302 D303 D304 D305 D306 D307 D308,D_x2_ACom_KKA,SOT-23,7,
11,LED generic,LED,D401 D402 D403 D404 D405 D406 D407 D408 D409 D410 D411 D412 D413 D414 D415 D416 D417,SML-D12Y1WT86,LED_0603,17,
12,Spark Gap,SPARK_GAP,E101 E102,SPARK_GAP,B88069X4911T902,2,
13,"Generic connector, double row, 02x05, odd/even pin numbering scheme (row 1 odd numbers, row 2 even numbers)",Conn_02x05_Odd_Even,J105,Conn_02x05_Odd_Even,Pin_Header_Straight_2x05_Pitch2.54mm,1,
14,"coaxial connector (BNC, SMA, SMB, SMC, Cinch/RCA, ...)",Conn_Coaxial,J101 J102,Conn_Coaxial,BNC-5-1634503-1,2,
15,"coaxial connector (BNC, SMA, SMB, SMC, Cinch/RCA, ...)",Conn_Coaxial,J103,Conn_Coaxial,SMA_THT_Jack_Straight,1,
16,3-pin jumper/solder bridge,GS3,J106 J107 J108,GS3,GS3,3,
17,"Generic screw terminal, single row, 01x02",Screw_Terminal_01x02,J104,Screw_Terminal_01x02,TerminalBlock_bornier-2_P5.08mm,1,
18,Miniature Signal Relays,EE2-*TNU,K201 K202 K203 K204,EE2-*TNU,Relay_DPDT_DCLT,4,https://content.kemet.com/datasheets/KEM_R7002_EC2_EE2.pdf
19,Transistor PNP (general),ZXTP2006E6,Q401 Q402 Q403 Q404 Q405 Q406 Q407 Q408,ZXTP2006E6,SOT-23-6,8,
20,Resistor,R,R110 R111,100,R_0402,2,
21,Resistor,R,R212 R213 R215 R216 R229 R230 R233 R234,10k,R_0603,8,
22,Resistor,R,R227 R228 R435 R436 R437 R438 R439 R440 R441 R442,150,R_0805,10,
23,Resistor,R,R401 R402 R403 R404 R405 R406 R407 R408 R409 R410 R411 R412 R413 R414 R415 R416 R417 R418 R419 R420 R421 R422 R423 R424 R425 R426 R427 R428 R429 R430 R431 R432 R433 R434,18,R_0805,34,
24,Resistor,R,R105 R107 R108 R109,1k,R_0603,4,
25,Resistor,R,R101 R102 R103 R104 R201 R202 R203 R204 R205 R206 R207 R208,200,R_1206,12,
26,Resistor,R,R211 R214 R217 R218,20k,R_0603,4,
27,Resistor,R,R231 R232,22k,R_0603,2,
28,Resistor,R,R220 R224,390k,R_1206,2,
29,Resistor,R,R221 R222 R225 R226,50k,R_1206,4,
30,Resistor,R,R219 R223,510k,R_1206,2,
31,Resistor,R,R106,5k,R_0603,1,
32,Resistor,R,R209 R210,680,R_0603,2,
33,Resistor,R,R235 R236 R237 R238,82,R_0603,4,
34,"Push button switch, generic, two pins",SW_Push,SW302 SW303 SW304 SW306 SW307 SW308 SW309 SW310 SW311 SW312 SW313 SW314 SW315 SW316,SW_Push,SW_PUSH_6mm,14,
35,,10CL006ZE144I8G,U102,10CL006ZE144I8G,EQFP-144_20x20mm_Pitch0.5mm,1,
36,Single digit 16 segment yellow LED common anode right hand decimal,16Segment,U401 U402 U405 U406 U407 U408 U411 U412 U413 U416 U417 U418,16Segment,16Segment,12,
37,,LH1546,U203 U204,LH1546,SO-4_7.6x3.6mm_Pitch2.54mm,2,
38,"Switched capacitor inverter, inverts positive voltage +2.7 to +5.5V to negative, 200 mA, SOT-23-6",LM2776,U502,LM2776,SOT-23-6,1,http://www.ti.com/lit/ds/symlink/lm2776.pdf
39,Dual 700 ps High Speed Comparator with RSPECL Outputs,LMH7322,U206,LMH7322,QFN-24-1EP_4x4mm_Pitch0.5mm,1,
40,"High Voltage, High Current Darlington Transistor Arrays",MC1413,U205 U207 U403 U404 U409 U410 U414 U415,MC1413,SOIC-16_3.9x9.9mm_Pitch1.27mm,8,http://www.onsemi.com/pub_link/Collateral/MC1413-D.PDF
41,"Dual 8-bit Digital to Analog Converter, I2c Interface",MCP47FEBXX,U201,MCP47FEB02,TSSOP-8_4.4x3mm_Pitch0.65mm,1,http://ww1.microchip.com/downloads/en/DeviceDoc/20005375A.pdf
42,,SC183C,U419 U420 U421,SC183C,QFN-16-1EP_3x3mm_Pitch0.5mm,3,
43,,STM32_BLUEPILL,U101,STM32_BLUEPILL,DIP-40_W15.24mm,1,
44,"Dual Opamp, SOIC-8/DIP-8/SSOP-8/TO-99",Opamp_Dual_Generic,U202,TL972,TSSOP-8_3x3mm_Pitch0.65mm,1,





Component Groups:,44
Component Count:,239
Fitted Components:,239
Number of PCBs:,1
Total components:,239
Schematic Version:,
Schematic Date:,
BoM Date:,2018-02-04 23:40:10
Schematic Source:,D:\Dropbox\counter_kicad\counter\counter.sch
KiCad Version:,Eeschema (2018-02-03 revision 9c2230355)-makepkg

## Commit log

2020-01-03 initial
2020-01-03 new .gitignore
2020-01-03 add kicad hardware files
2020-01-03 add fpga code
